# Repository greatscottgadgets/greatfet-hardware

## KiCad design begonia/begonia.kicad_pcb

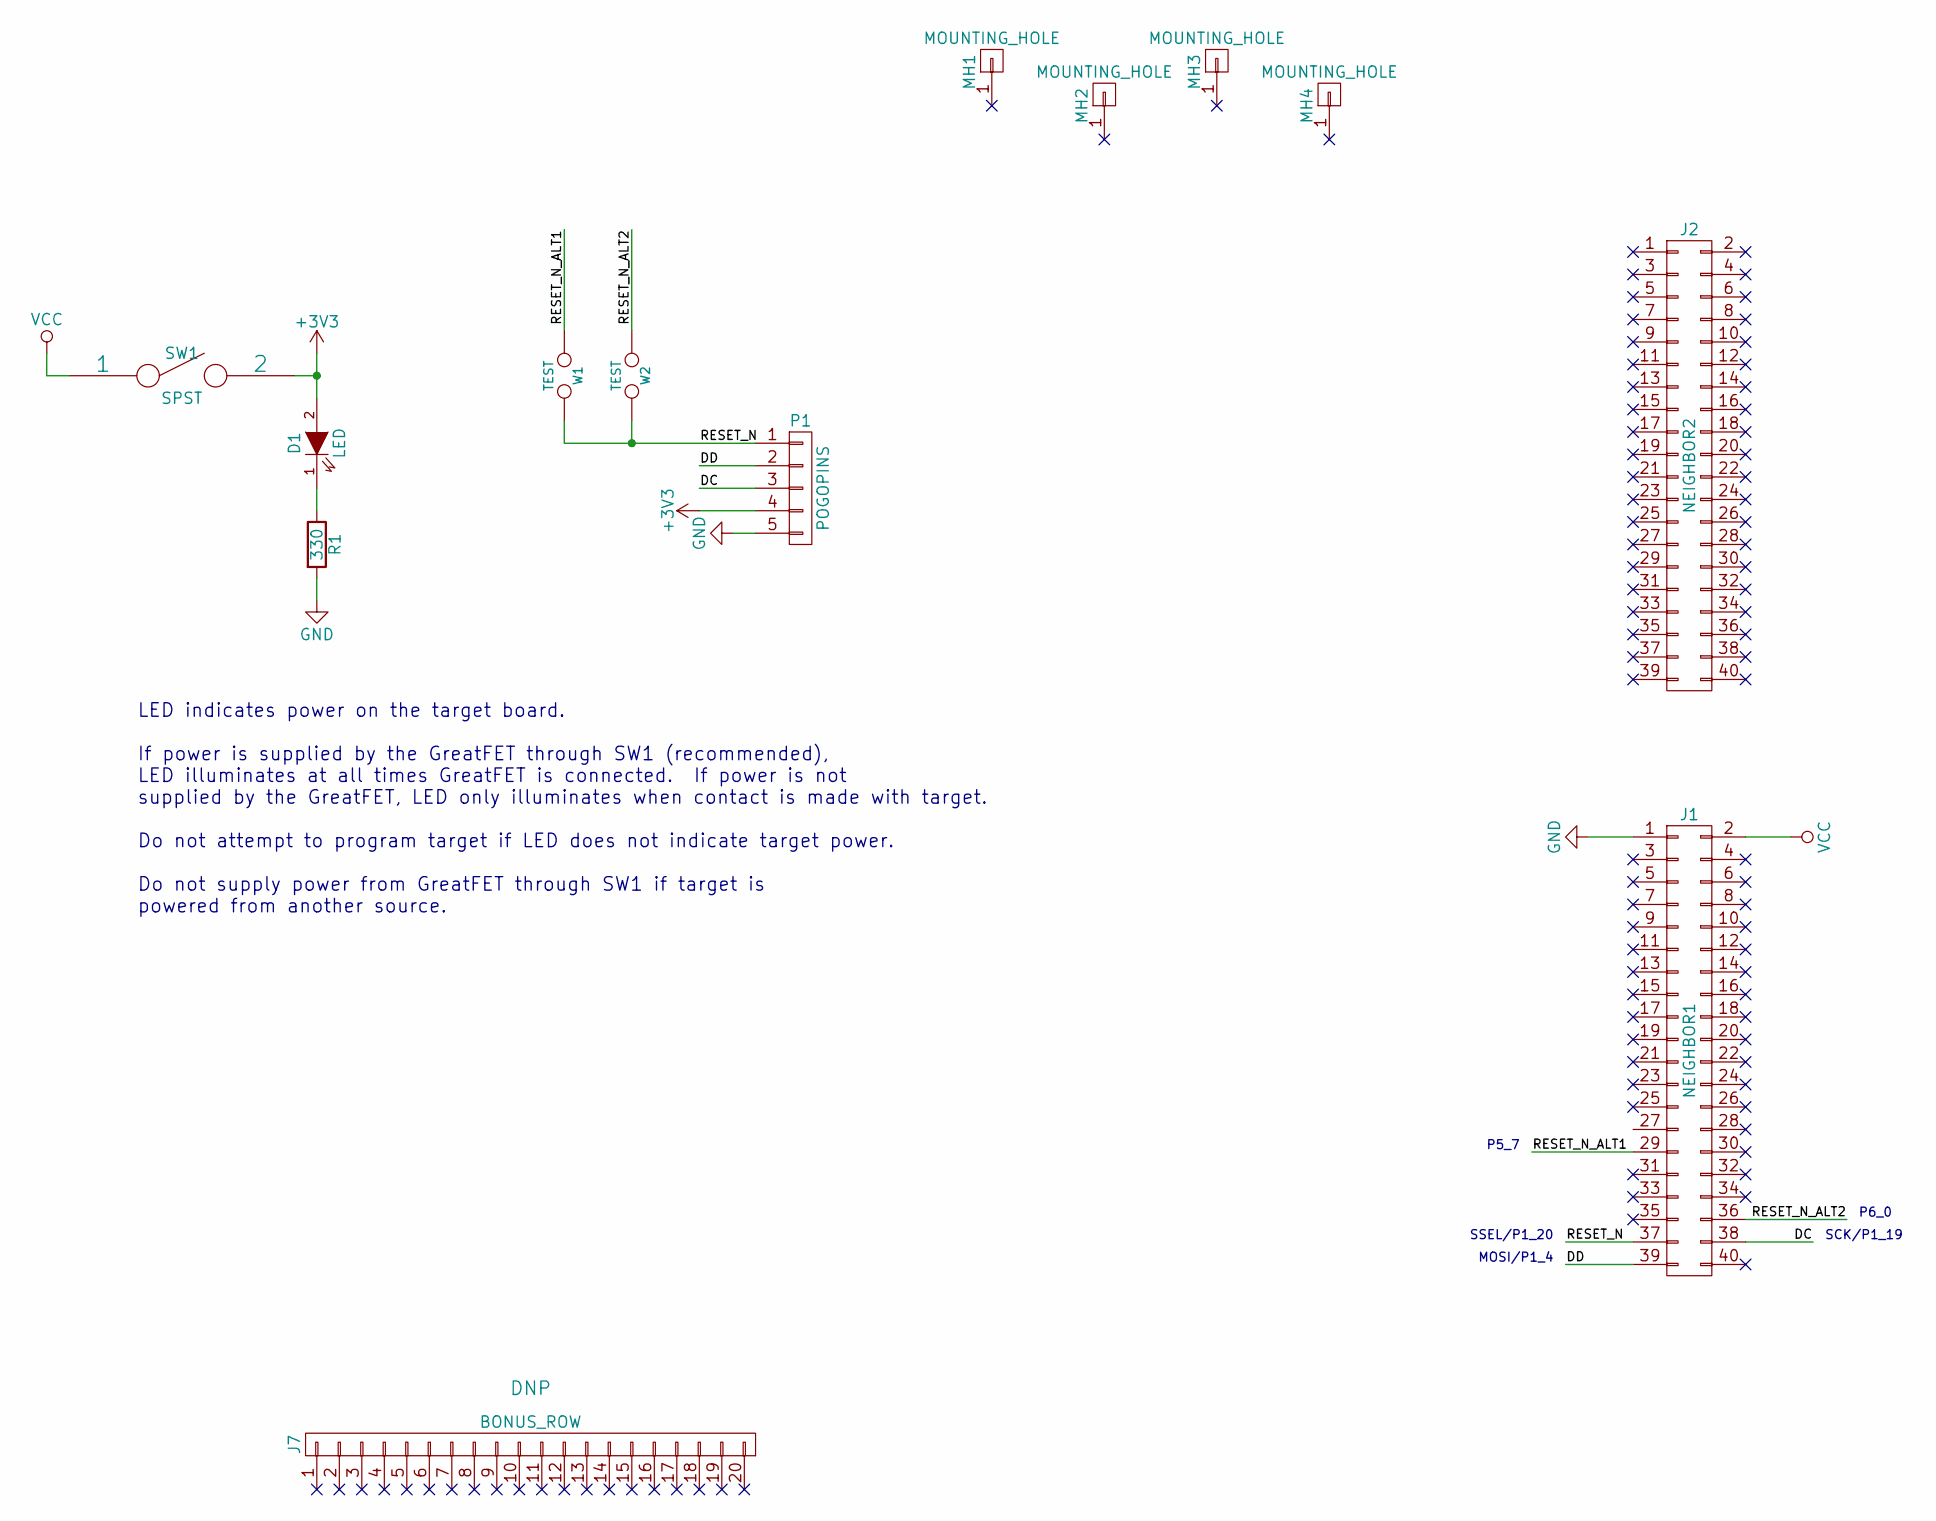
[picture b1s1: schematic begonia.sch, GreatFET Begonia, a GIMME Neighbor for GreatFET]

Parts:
D1: LED; 0603D; Part Number APT1608SGC
J1: NEIGHBOR1; HEADER-2x20; Part Number SSQ-120-23-G-D
J2: NEIGHBOR2; HEADER-2x20; Part Number SSQ-120-23-G-D
J7: BONUS_ROW; HEADER-1x20; Part Number SSQ-120-23-G-S
MH1, MH2, MH3, MH4: MOUNTING_HOLE; HOLE126MIL-COPPER
P1: POGOPINS; POGOPIN-5-IMME; Part Number PRT-09174
R1: 330; 0603; Part Number RMCF0603JT330R
SW1: SPST; SSSS810701; Part Number SSSS810701
W1, W2: TEST; 0603-JUMPER

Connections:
+3V3: D1.2 (A), P1.4, SW1.2
/DC: J1.38, P1.3
/DD: J1.39, P1.2
/RESET_N: J1.37, P1.1, W1.2, W2.2
/RESET_N_ALT1: J1.29, W1.1
/RESET_N_ALT2: J1.36, W2.1
GND: J1.1, P1.5, R1.2
unnamed: D1.1 (K), R1.1
VCC: J1.2, SW1.1

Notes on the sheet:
MOSI/P1_4
SCK/P1_19
SSEL/P1_20
LED indicates power on the target board. If power is supplied by the GreatFET through SW1 (recommended), LED illuminates at all times GreatFET is connected. If power is not supplied by the GreatFET, LED only illuminates when contact is made with target. Do not attempt to program target if LED does 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
P5_7
P6_0

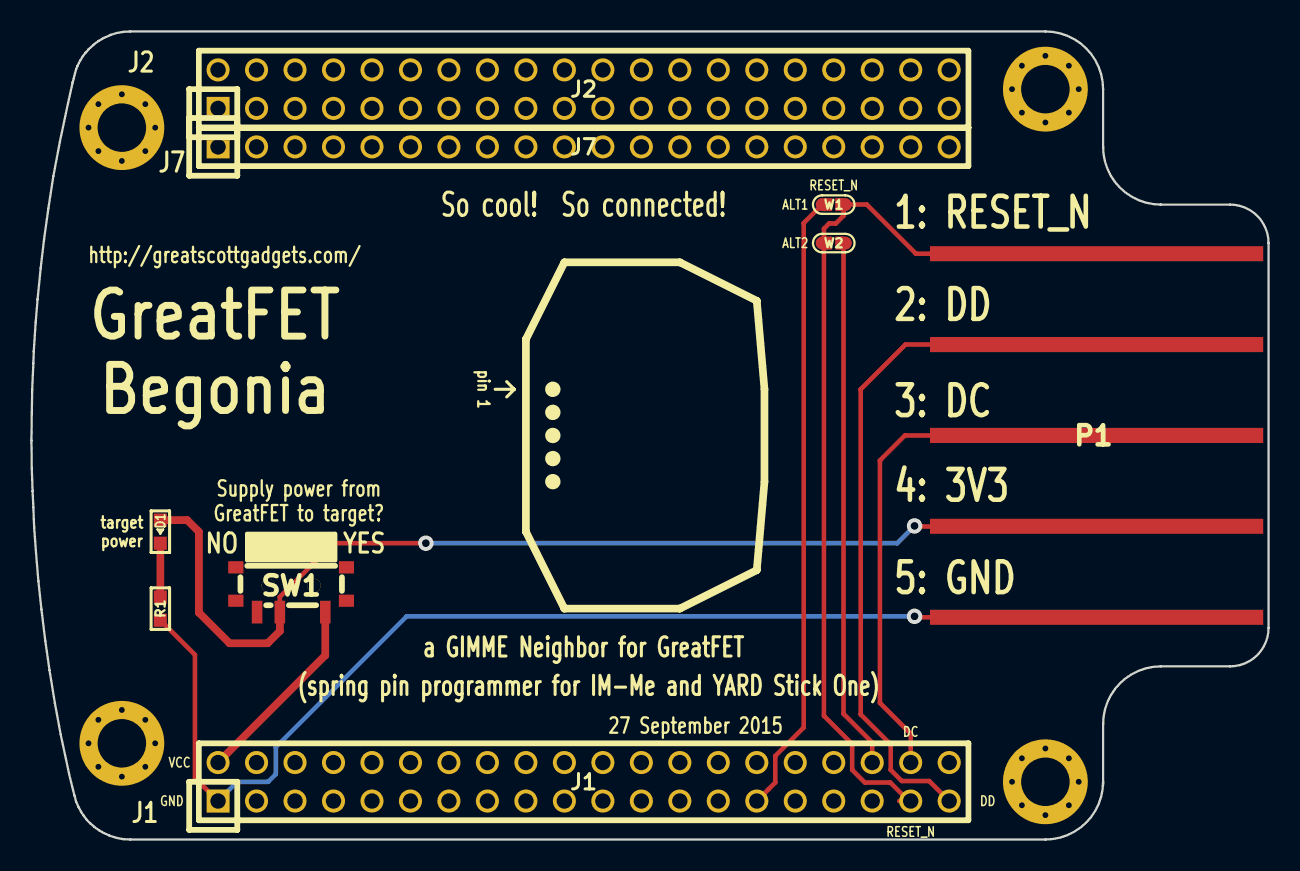
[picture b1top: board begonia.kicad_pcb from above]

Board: 2 copper layers, 81.7 x 53.3 mm, 13 parts (0 on the bottom side), 9 nets.

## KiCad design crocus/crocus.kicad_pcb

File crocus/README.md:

# GreatFET Crocus
A GreatFET Neighbor for the Nordic nRF24L01+

Required KiCad dependency:

https://github.com/greatscottgadgets/gsg-kicad-lib

If you are using git, the preferred way to install gsg-kicad-lib is to use the
submodule:

$ git submodule init && git submodule update

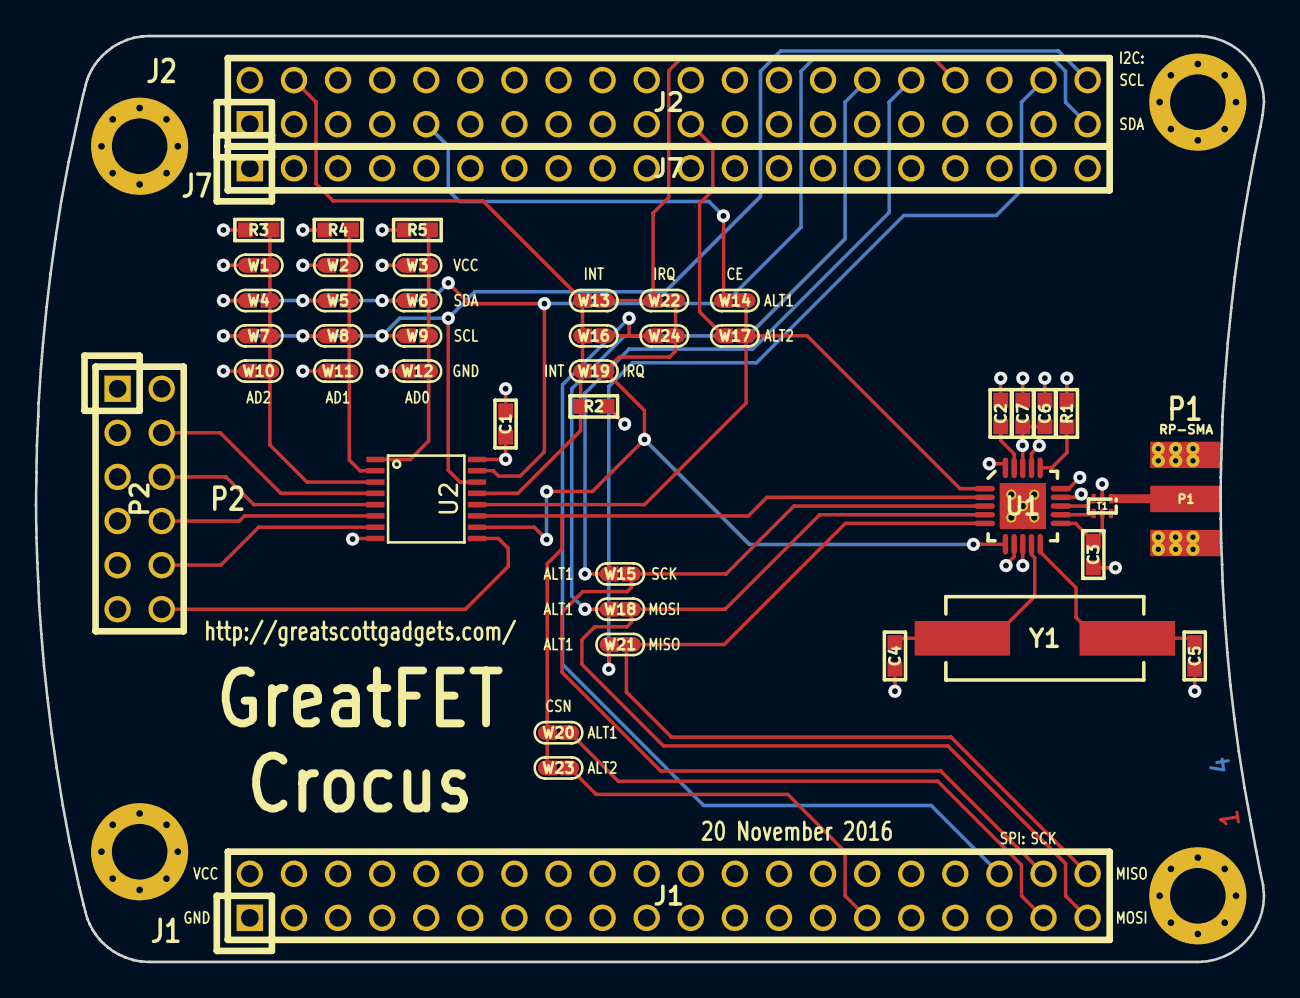
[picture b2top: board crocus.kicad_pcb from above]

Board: 4 copper layers, 70.7 x 53.3 mm, 49 parts (0 on the bottom side), 36 nets.

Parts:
C1, C2: 33nF; 0603
C3: 2.2nF; 0603
C4, C5: 18pF; 0603
C6: 10nF; 0603
C7: 1nF; 0603
J1: NEIGHBOR1; HEADER-2x20
J2: NEIGHBOR2; HEADER-2x20
J7: BONUS_ROW; HEADER-1x20
MH1, MH2, MH3, MH4: MOUNTING_HOLE; HOLE126MIL-COPPER
P1: RP-SMA; SMA-EDGE
P2: EXPANSION; HEADER-2x6
R1: 22.0k; 0603
R2, R3, R4, R5: 10k; 0603
T1: BALUN; 2500BL14M100
U1: nRF24L01+; QFN20-4
U2: PCA9674; TSSOP16
W1, W2, W3, W4, W5, W6, W7, W8, W9, W10, W11, W12, W13, W14, W15, W16, W17, W18, W19, W20, W21, W22, W23, W24: TEST; 0603-JUMPER
Y1: XTAL; HC-49S

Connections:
/AD0: R5.1, U2.1, W3.2, W6.2, W9.2, W12.2
/AD1: R4.1, U2.2, W2.2, W5.2, W8.2, W11.2
/AD2: R3.1, U2.3, W1.2, W4.2, W7.2, W10.2
/ANT1: T1.4, U1.12
/ANT2: T1.3, U1.13
/CE: U1.1, U2.12, W14.2, W17.2
/CE_ALT1: J2.9, W14.1
/CE_ALT2: J2.21, W17.1
/CSN: U1.2, U2.11, W20.2, W23.2
/CSN_ALT1: J1.37, W20.1
/CSN_ALT2: J1.29, W23.1
/DVDD: C2.1, U1.19
/I2C0_SCL: J2.40, U2.14, W7.1, W8.1, W9.1
/I2C0_SDA: J2.39, U2.15, W4.1, W5.1, W6.1
/INT: J2.4, R2.2, U2.13, W13.2, W16.2, W19.1
/INT_ALT1: J2.34, W13.1, W22.1
/INT_ALT2: J1.36, W16.1, W24.1
/IREF: R1.2, U1.16
/IRQ: U1.6, U2.10, W19.2, W22.2, W24.2
/MISO: J1.40, U1.5, W21.2
/MISO_ALT1: J2.38, W21.1
/MOSI: J1.39, U1.4, W18.2
/MOSI_ALT1: J2.30, W18.1
/P0: P2.4, U2.4
/P1: P2.6, U2.5
/P2: P2.8, U2.6
/P3: P2.10, U2.7
/P4: P2.12, U2.9
/RF: P1.1, T1.1
/SCK: J1.38, U1.3, W15.2
/SCK_ALT1: J2.32, W15.1
/VDD_PA: C3.1, T1.5, U1.11
/XC1: C5.1, U1.10, Y1.2
/XC2: C4.1, U1.9, Y1.1
GND: C1.2, C2.2, C3.2, C4.2, C5.2, C6.2, C7.2, J1.1, MH1.1, MH2.1, MH3.1, MH4.1, P1.2, P2.1, P2.3, P2.5, P2.7, P2.9, P2.11, R1.1, R3.2, R4.2, R5.2, T1.2, U1.8, U1.14, U1.17, U1.20, U2.8, W10.1, W11.1, W12.1
VCC: C1.1, C6.1, C7.1, J1.2, P2.2, R2.1, U1.7, U1.15, U1.18, U2.16, W1.1, W2.1, W3.1

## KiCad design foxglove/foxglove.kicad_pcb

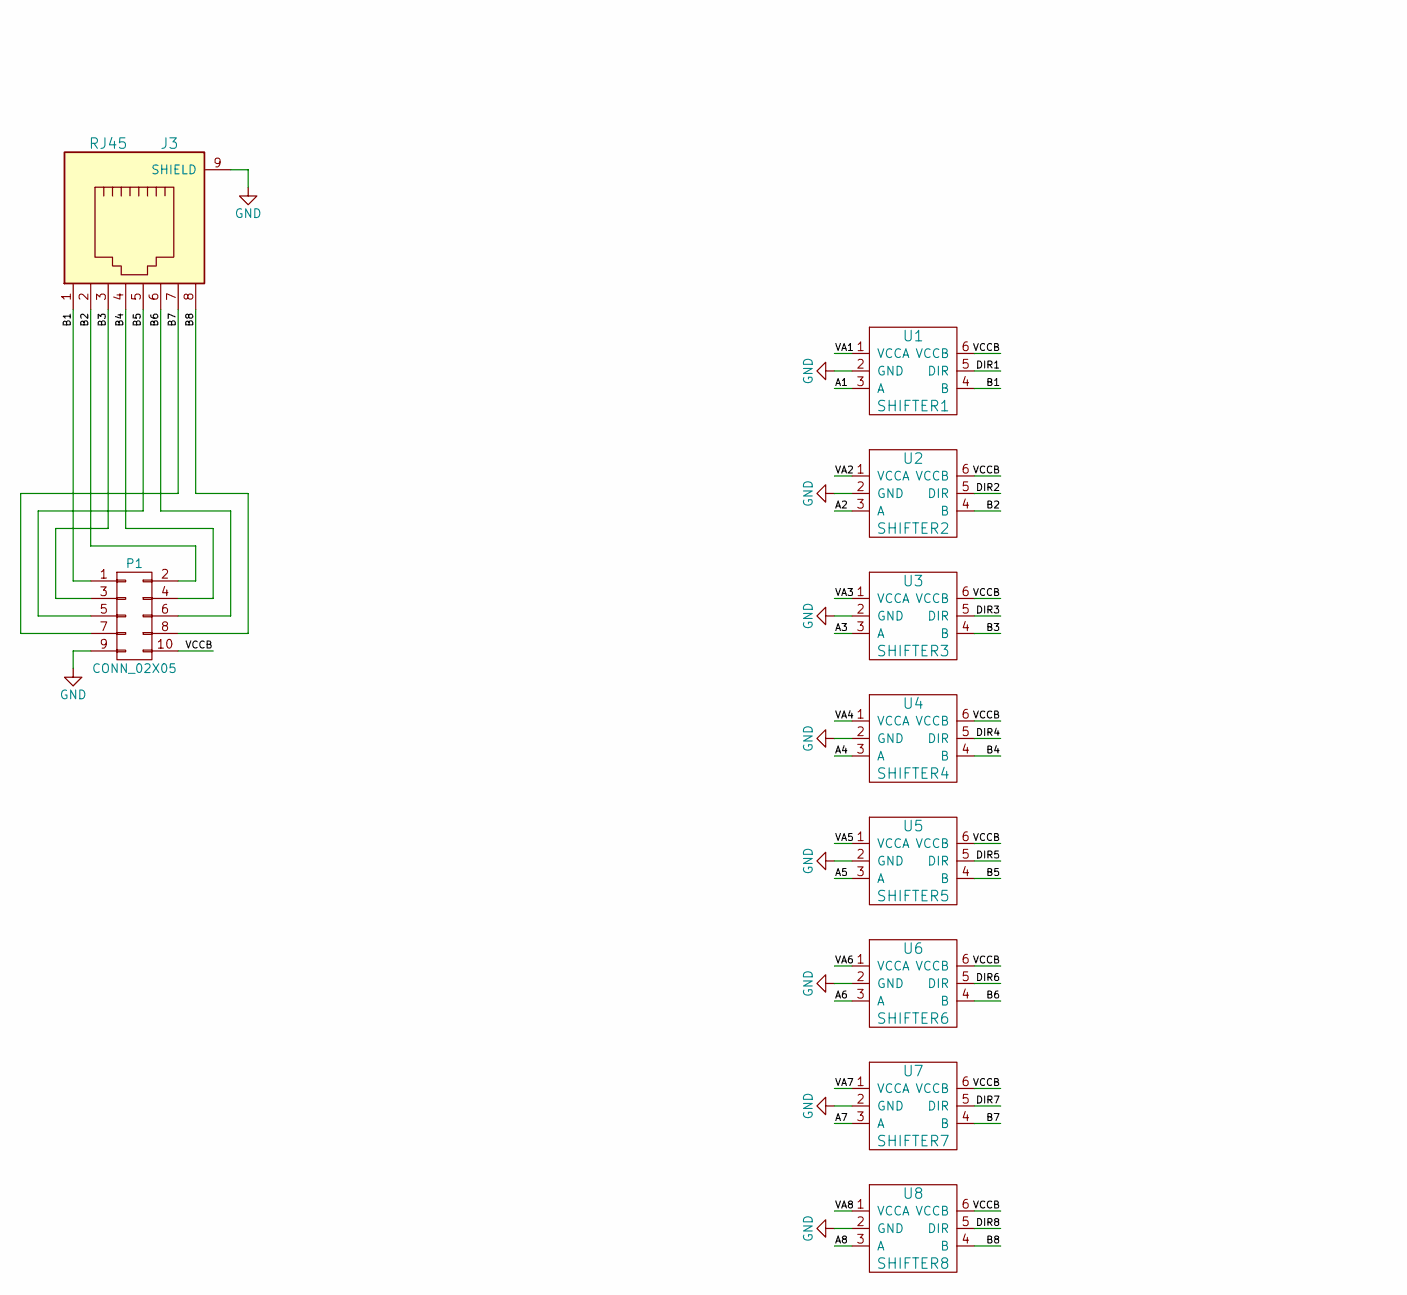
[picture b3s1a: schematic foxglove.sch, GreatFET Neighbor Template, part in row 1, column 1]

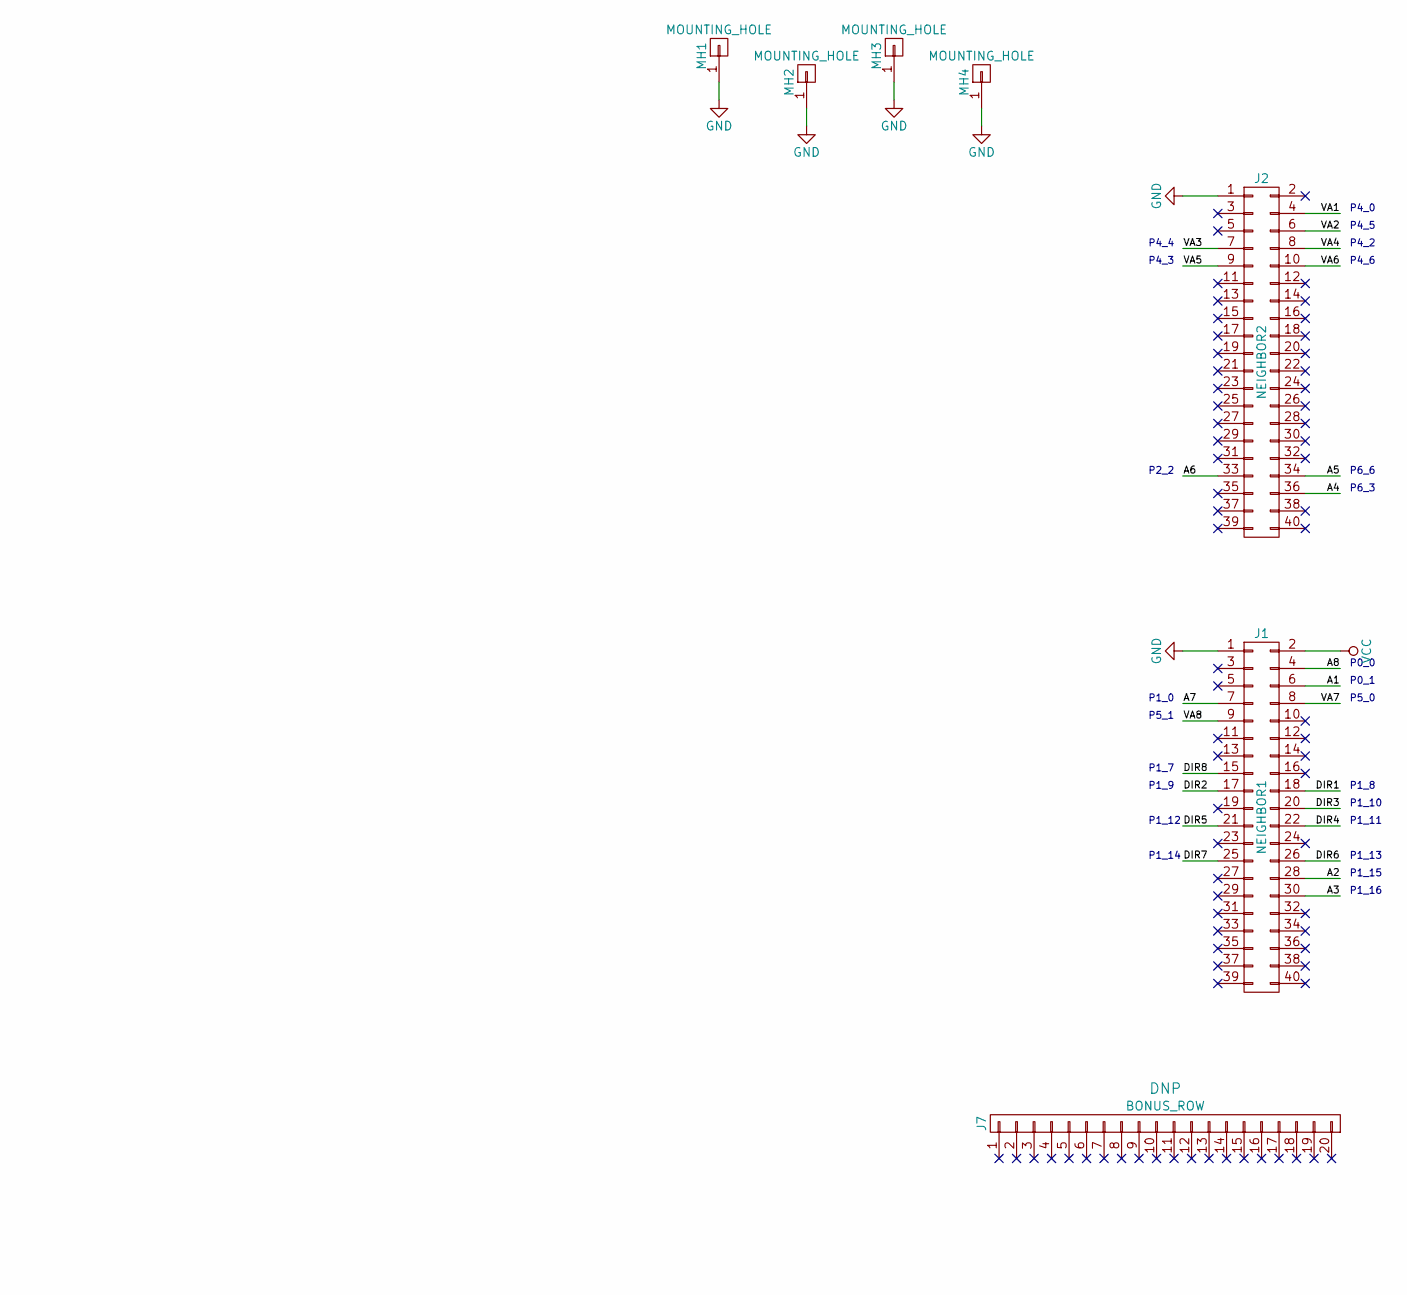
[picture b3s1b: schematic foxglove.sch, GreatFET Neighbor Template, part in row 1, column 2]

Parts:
J1: NEIGHBOR1; HEADER-2x20; Part Number SSQ-120-23-G-D
J2: NEIGHBOR2; HEADER-2x20; Part Number SSQ-120-23-G-D
J3: RJ45; RJ45-RJHSE-5380
J7: BONUS_ROW; HEADER-1x20; Part Number SSQ-120-23-G-S
MH1, MH2, MH3, MH4: MOUNTING_HOLE; HOLE126MIL-COPPER
P1: CONN_02X05; HEADER-2x5
U1: SHIFTER1; SOT363; Part Number 74LVCH1T45GW,125
U2: SHIFTER2; SOT363; Part Number 74LVCH1T45GW,125
U3: SHIFTER3; SOT363; Part Number 74LVCH1T45GW,125
U4: SHIFTER4; SOT363; Part Number 74LVCH1T45GW,125
U5: SHIFTER5; SOT363; Part Number 74LVCH1T45GW,125
U6: SHIFTER6; SOT363; Part Number 74LVCH1T45GW,125
U7: SHIFTER7; SOT363; Part Number 74LVCH1T45GW,125
U8: SHIFTER8; SOT363; Part Number 74LVCH1T45GW,125

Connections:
/A1: J1.6, U1.3 (A)
/A2: J1.28, U2.3 (A)
/A3: J1.30, U3.3 (A)
/A4: J2.36, U4.3 (A)
/A5: J2.34, U5.3 (A)
/A6: J2.33, U6.3 (A)
/A7: J1.7, U7.3 (A)
/A8: J1.4, U8.3 (A)
/B1: J3.1, P1.1, U1.4 (B)
/B2: J3.2, P1.2, U2.4 (B)
/B3: J3.3, P1.3, U3.4 (B)
/B4: J3.4, P1.4, U4.4 (B)
/B5: J3.5, P1.5, U5.4 (B)
/B6: J3.6, P1.6, U6.4 (B)
/B7: J3.7, P1.7, U7.4 (B)
/B8: J3.8, P1.8, U8.4 (B)
/DIR1: J1.18, U1.5 (DIR)
/DIR2: J1.17, U2.5 (DIR)
/DIR3: J1.20, U3.5 (DIR)
/DIR4: J1.22, U4.5 (DIR)
/DIR5: J1.21, U5.5 (DIR)
/DIR6: J1.26, U6.5 (DIR)
/DIR7: J1.25, U7.5 (DIR)
/DIR8: J1.15, U8.5 (DIR)
/VA1: J2.4, U1.1 (VCCA)
/VA2: J2.6, U2.1 (VCCA)
/VA3: J2.7, U3.1 (VCCA)
/VA4: J2.8, U4.1 (VCCA)
/VA5: J2.9, U5.1 (VCCA)
/VA6: J2.10, U6.1 (VCCA)
/VA7: J1.8, U7.1 (VCCA)
/VA8: J1.9, U8.1 (VCCA)
/VCCB: P1.10, U1.6 (VCCB), U2.6 (VCCB), U3.6 (VCCB), U4.6 (VCCB), U5.6 (VCCB), U6.6 (VCCB), U7.6 (VCCB), U8.6 (VCCB)
GND: J1.1, J2.1, J3.9 (SHIELD), MH1.1, MH2.1, MH3.1, MH4.1, P1.9, U1.2 (GND), U2.2 (GND), U3.2 (GND), U4.2 (GND), U5.2 (GND), U6.2 (GND), U7.2 (GND), U8.2 (GND); also elsewhere on the board
VCC: J1.2; also elsewhere on the board

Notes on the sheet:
P0_0
P0_1
P1_15
P1_16
P6_3
P6_6
P1_0
P1_7
P1_8
P1_9
P1_10
P1_11
P1_12
P1_13
P1_14
P2_2
P4_0
P4_5
P4_2
P4_6
P4_4
P4_3
P5_0
P5_1

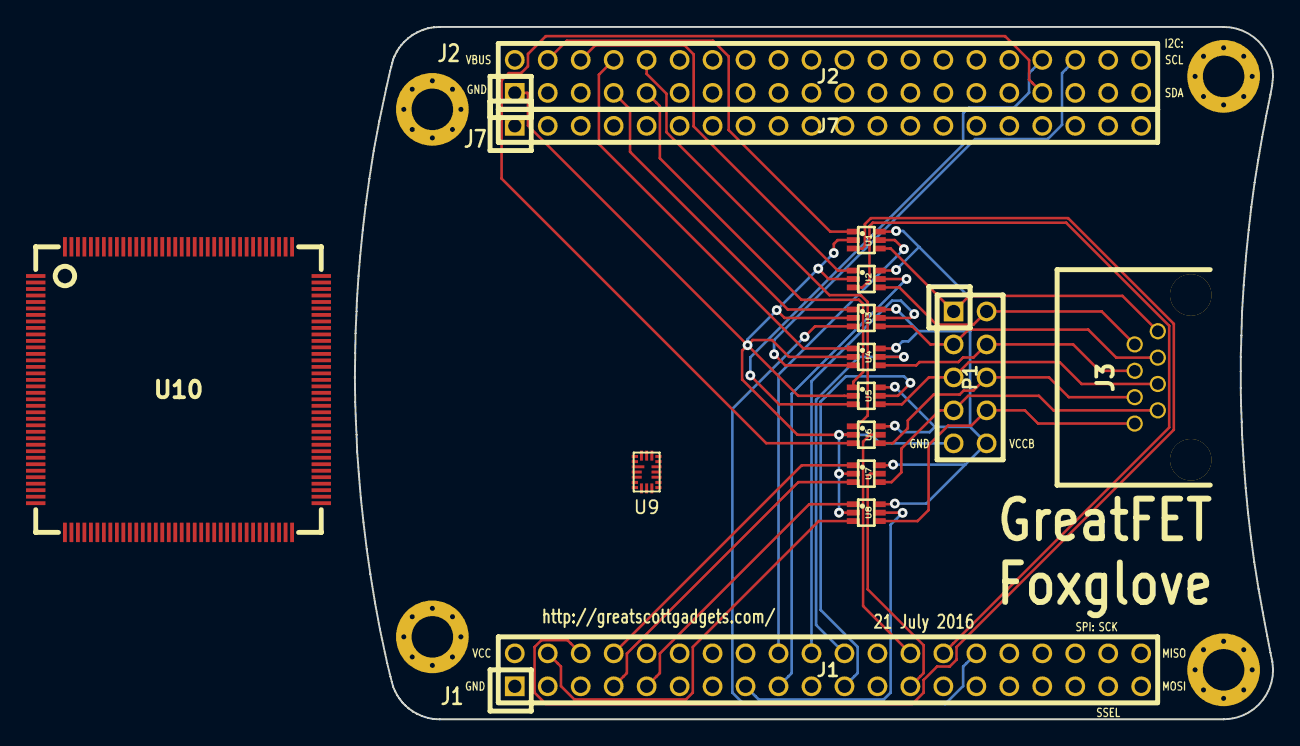
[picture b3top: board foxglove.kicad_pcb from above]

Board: 2 copper layers, 70.7 x 53.3 mm, 19 parts (0 on the bottom side), 35 nets.

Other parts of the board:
U9: SLG46621
U10: iCE40HX4K; LQFP144

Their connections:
GND: U9.11; also elsewhere on the board
VCC: U9.1; also elsewhere on the board

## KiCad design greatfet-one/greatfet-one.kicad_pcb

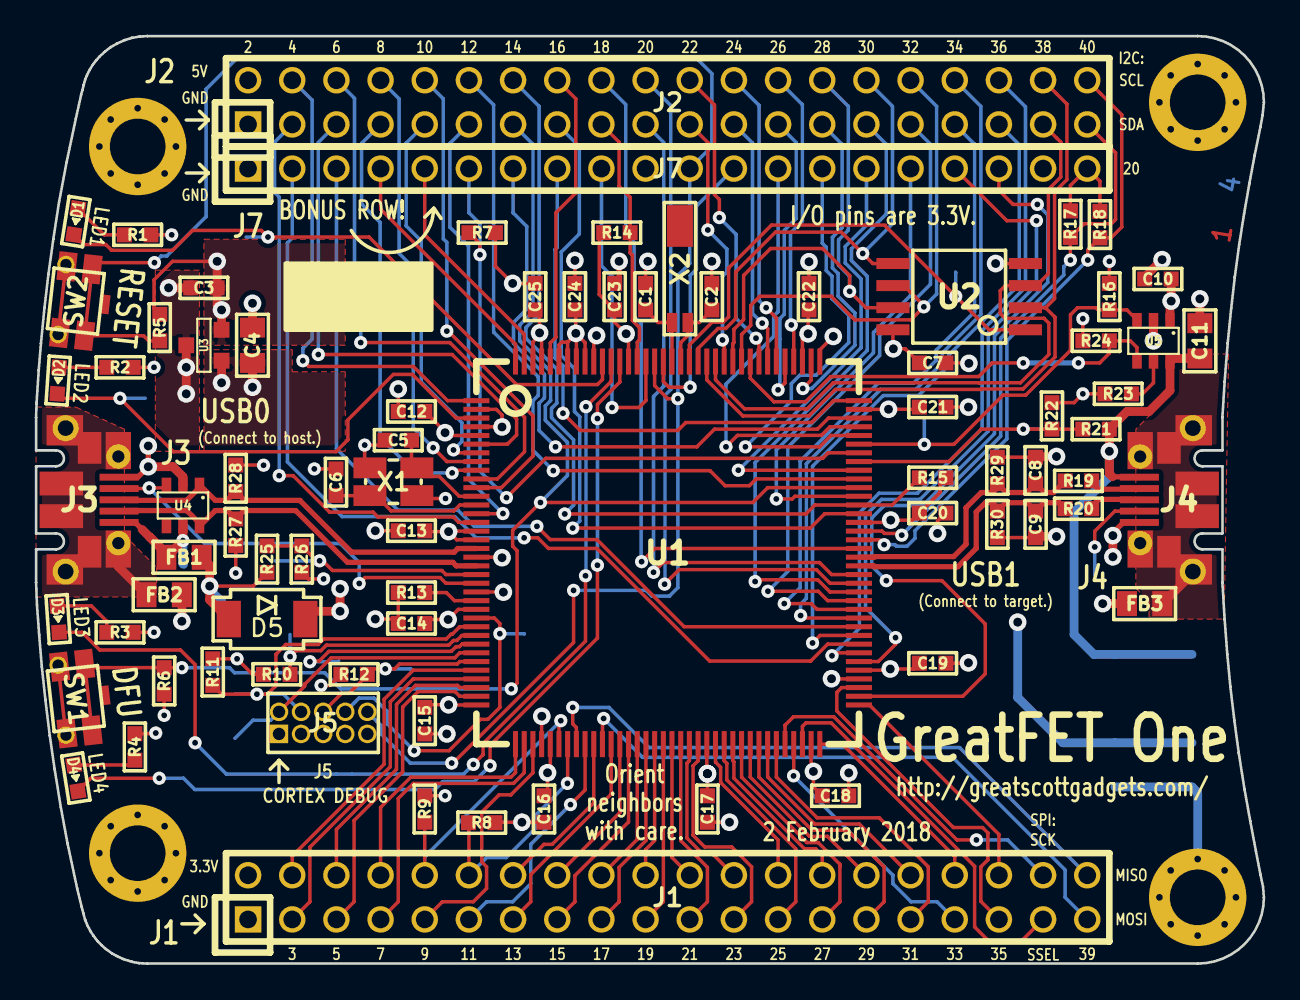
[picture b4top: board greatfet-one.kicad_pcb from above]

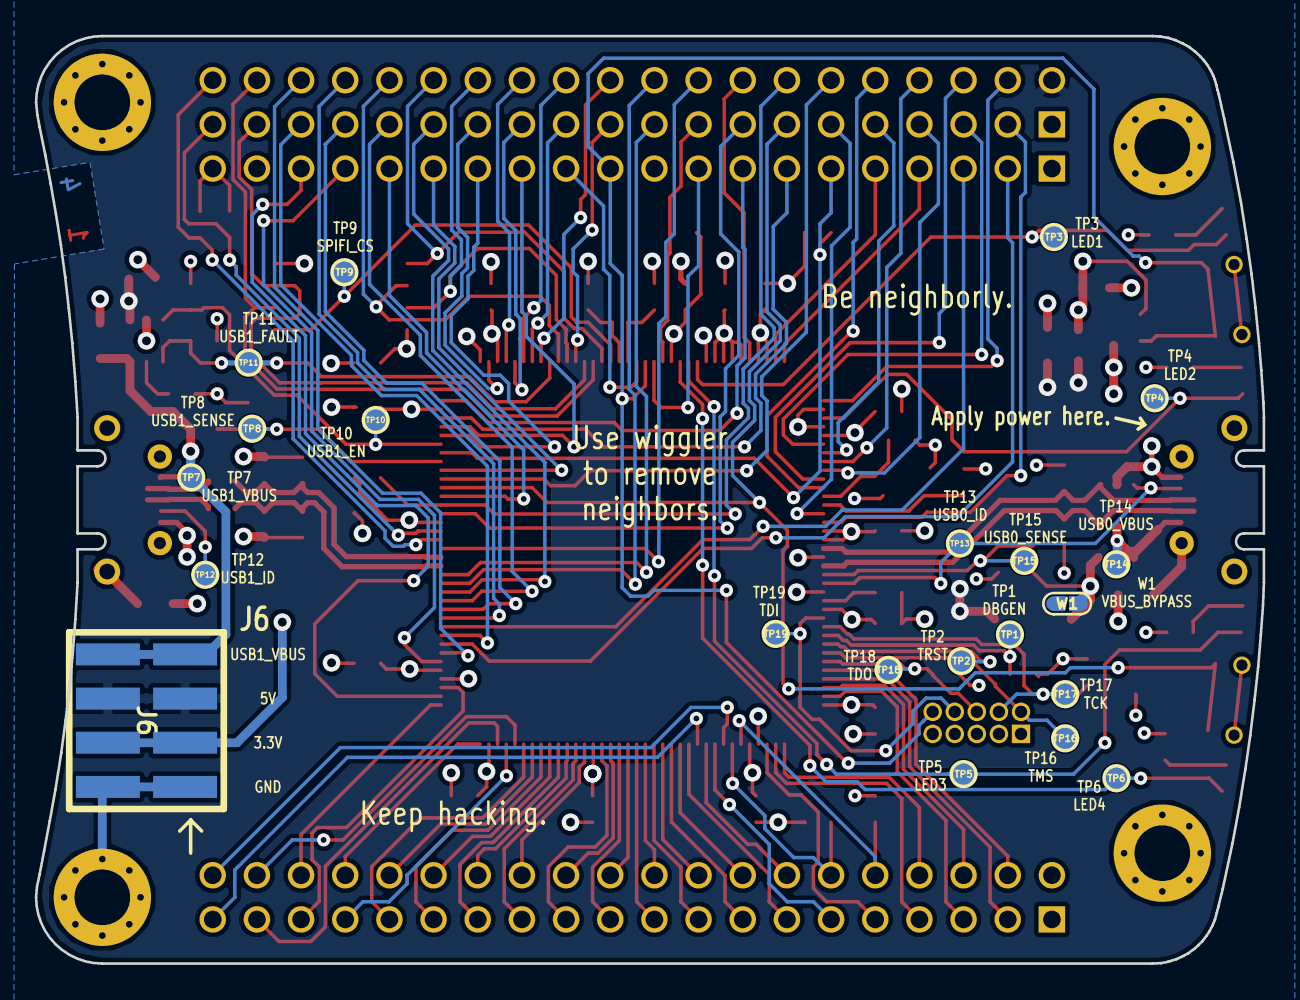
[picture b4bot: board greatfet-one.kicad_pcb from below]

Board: 4 copper layers, 70.6 x 53.3 mm, 103 parts (21 on the bottom side), 133 nets.

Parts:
C1, C2, C5, C6, C8, C9: 18pF; 0603
C3, C10: 1uF; 0603
C4, C11: 10uF; 0805
C7, C12, C13, C14, C15, C16, C17, C18, C19, C20, C21, C22, C23, C24, C25: 100nF; 0603
D1: LED1; 0603D
D2: LED2; 0603D
D3: LED3; 0603D
D4: LED4; 0603D
D5: VBUS_DIODE; SOD128
FB1, FB2, FB3: FILTER; 0805
J1: NEIGHBOR1; HEADER-2x20
J2: NEIGHBOR2; HEADER-2x20
J3, J4: USB-MICRO-B-SHIELDED; USB-MICROB-FCI-10103592-LONGPADS
J5: JTAG; 50MIL-HEADER-2x5-TH
J6: POWER; HEADER-SMT-2x4
J7: BONUS_ROW; HEADER-1x20
MH1, MH2, MH3, MH4: MOUNTING_HOLE; HOLE126MIL-COPPER
R1, R2, R3, R4: 330; 0603
R5, R6, R7, R8, R9, R10, R11, R12, R14, R15, R16, R21, R24, R25: 10k; 0603
R13: 12.0k; 0603
R17, R18: 1.8k; 0603
R19, R20: 33.0; 0603
R22, R26: 18k; 0603
R23: 43.2k; 0603
R27, R28, R29, R30: 15k; 0603
SW1: DFU; SWITCH-PTS840-P
SW2: RESET; SWITCH-PTS840-P
TP1: DBGEN; TESTPOINT-50MIL
TP2: TRST; TESTPOINT-50MIL
TP3: LED1; TESTPOINT-50MIL
TP4: LED2; TESTPOINT-50MIL
TP5: LED3; TESTPOINT-50MIL
TP6: LED4; TESTPOINT-50MIL
TP7: USB1_VBUS; TESTPOINT-50MIL
TP8: USB1_SENSE; TESTPOINT-50MIL
TP9: SPIFI_CS; TESTPOINT-50MIL
TP10: USB1_EN; TESTPOINT-50MIL
TP11: USB1_FAULT; TESTPOINT-50MIL
TP12: USB1_ID; TESTPOINT-50MIL
TP13: USB0_ID; TESTPOINT-50MIL
TP14: USB0_VBUS; TESTPOINT-50MIL
TP15: USB0_SENSE; TESTPOINT-50MIL
TP16: TMS; TESTPOINT-50MIL
TP17: TCK; TESTPOINT-50MIL
TP18: TDO; TESTPOINT-50MIL
TP19: TDI; TESTPOINT-50MIL
U1: LPC4330FBD144; LQFP144
U2: W25Q16DV; SOIC8-208
U3: AP7333; SOT23-3
U4: IP4220CZ6; SOT457
U5: AP2553W6-7; SOT457
W1: VBUS_BYPASS; 0603-JUMPER
X1: MCU_XTAL; XTAL3.2x2.5mm-EXT
X2: RTC_XTAL; XTAL-AB26TRQ

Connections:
+5V: C4.1, C10.1, D5.1, J2.2, J6.5, J6.6, U3.1, U5.1, W1.1
/ADC0_0: J2.5, U1.6
/ADC0_2: J7.5, U1.143
/ADC0_5: J7.4, U1.144
/CLK0: J1.11, U1.45
/CLK2: J2.12, U1.99
/DBGEN: R10.2, TP1.1, U1.28
/I2C0_SCL: J2.40, R18.2, U1.92
/I2C0_SDA: J2.39, R17.2, U1.93
/LED1: D1.1, TP3.1, U1.134
/LED2: D2.1, TP4.1, U1.3
/LED3: D3.1, TP5.1, U1.133
/LED4: D4.1, TP6.1, U1.132
/P0_0: J1.4, U1.32
/P0_1: J1.6, U1.34
/P1_0: J1.7, U1.38
/P1_1: J1.10, R9.2, U1.42
/P1_2: J1.12, R8.1, U1.43
/P1_3: J1.40, U1.44
/P1_4: J1.39, U1.47
/P1_5: J1.13, U1.48
/P1_6: J1.16, U1.49
/P1_7: J1.15, U1.50
/P1_8: J1.18, U1.51
/P1_9: J1.17, U1.52
/P1_10: J1.20, U1.53
/P1_11: J1.22, U1.55
/P1_12: J1.21, U1.56
/P1_13: J1.26, U1.60
/P1_14: J1.25, U1.61
/P1_15: J1.28, U1.62
/P1_16: J1.30, U1.64
/P1_17: J1.32, U1.66
/P1_18: J1.31, U1.67
/P1_19: J1.38, U1.68
/P1_20: J1.37, U1.70
/P2_0: J1.35, U1.75
/P2_1: J2.35, U1.81
/P2_2: J2.33, U1.84
/P2_3: J2.20, U1.87
/P2_4: J2.19, U1.88
/P2_5: J2.18, U1.91
/P2_6: J2.15, U1.95
/P2_7: J2.14, R15.2, U1.96
/P2_8: J2.13, R6.1, SW1.1, U1.98
/P2_9: J7.6, R7.1, U1.102
/P2_10: J7.14, U1.104
/P2_11: J7.13, U1.105
/P2_12: J7.7, U1.106
/P2_13: J7.8, U1.108
/P3_0: J2.26, U1.112
/P3_1: J2.24, U1.114
/P3_2: J2.22, U1.116
/P3_3: J2.32, U1.118, U2.6
/P3_4: J2.28, U1.119, U2.7
/P3_5: J2.37, U1.121, U2.3
/P3_6: J2.38, U1.122, U2.2
/P3_7: J2.30, U1.123, U2.5
/P4_0: J2.4, U1.1
/P4_2: J2.8, U1.8
/P4_3: J2.9, U1.7
/P4_4: J2.7, U1.9
/P4_5: J2.6, U1.10
/P4_6: J2.10, U1.11
/P4_7: J2.11, U1.14
/P4_8: J2.3, U1.15
/P4_9: J1.3, U1.33
/P4_10: J1.5, U1.35
/P5_0: J1.8, U1.37
/P5_1: J1.9, U1.39
/P5_2: J1.14, U1.46
/P5_3: J1.19, U1.54
/P5_4: J1.24, U1.57
/P5_5: J1.23, U1.58
/P5_6: J1.27, U1.63
/P5_7: J1.29, U1.65
/P6_0: J1.36, U1.73
/P6_1: J7.18, U1.74
/P6_2: J7.17, U1.78
/P6_3: J2.36, U1.79
/P6_4: J7.2, U1.80
/P6_5: J7.3, U1.82
/P6_6: J2.34, U1.83
/P6_7: J2.31, U1.85
/P6_8: J2.29, U1.86
/P6_9: J7.16, U1.97
/P6_10: J7.15, U1.100
/P7_0: J2.27, U1.110
/P7_1: J2.25, U1.113
/P7_2: J2.23, U1.115
/P7_7: J2.16, U1.140
/P9_5: J1.33, U1.69
/P9_6: J1.34, U1.72
/PF_4: J2.21, U1.120
/RESET: J5.10, J7.11, R5.2, SW2.1, U1.128
/RTCX1: C2.1, U1.125, X2.2
/RTCX2: C1.1, U1.126, X2.1
/RTC_ALARM: J7.9, U1.129
/SPIFI_CS: TP9.1, U1.124, U2.1
/TCK: J5.4, R11.2, TP17.1, U1.27
/TDI: J5.8, TP19.1, U1.26
/TDO: J5.6, R12.2, TP18.1, U1.31
/TMS: J5.2, TP16.1, U1.30
/TRST: TP2.1, U1.29
/USB0_D+: J3.3, R28.1, U1.18, U4.1
/USB0_D-: J3.2, R27.1, U1.20, U4.6
/USB0_ID: J3.4, TP13.1, U1.22, U4.3
/USB0_SENSE: R25.2, R26.2, TP15.1, U1.21
/USB0_SHIELD: FB2.2, J3.0
/USB0_VBUS: FB1.1, J3.1, TP14.1, U4.5
/USB1_D+: C9.1, R20.2, R30.1, U1.89
/USB1_D-: C8.1, R19.2, R29.1, U1.90
/USB1_EN: R16.2, TP10.1, U1.103, U5.3
/USB1_FAULT: R24.1, TP11.1, U1.117, U5.4
/USB1_ID: J4.4, TP12.1
/USB1_SENSE: R21.2, R22.2, TP8.1, U1.101
/USB1_SHIELD: FB3.1, J4.0
/USB1_VBUS: C11.1, J4.1, J6.7, J6.8, R21.1, TP7.1, U5.6
/VBAT: J7.12, U1.127
/WAKEUP0: J2.17, R14.2, U1.130
GND: C1.2, C2.2, C3.2, C4.2, C5.2, C6.2, C7.2, C8.2, C9.2, C10.2, C11.2, C12.2, C13.2, C14.2, C15.2, C16.2, C17.2, C18.2, C19.2, C20.2, C21.2, C22.2, C23.2, C24.2, C25.2, FB2.1, FB3.2, J1.1, J2.1, J3.5, J4.5, J5.3, J5.5, J5.9, J6.1, J6.2, J7.1, J7.10, J7.19, MH1.1, MH2.1, MH3.1, MH4.1, R6.2, R7.2, R8.2, R13.2, R16.1, R22.1, R23.1, R26.1, R27.2, R28.2, R29.2, R30.2, SW2.2, U1.2, U1.4, U1.19, U1.23, U1.40, U1.76, U1.109, U1.135, U2.4, U3.3, U4.2, U5.2, X1.2, X1.4
unnamed: C5.1, U1.12, X1.1
unnamed: C6.1, U1.13, X1.3
unnamed: D1.2, R1.2
unnamed: D2.2, R2.2
unnamed: D3.2, R3.2
unnamed: D4.2, R4.2
unnamed: D5.2, FB1.2, R25.1, W1.2
unnamed: J4.2, R19.1
unnamed: J4.3, R20.1
unnamed: R13.1, U1.24
unnamed: R23.2, U5.5
VCC: C3.1, C7.1, C12.1, C13.1, C14.1, C15.1, C16.1, C17.1, C18.1, C19.1, C20.1, C21.1, C22.1, C23.1, C24.1, C25.1, J1.2, J5.1, J6.3, J6.4, J7.20, R1.1, R2.1, R3.1, R4.1, R5.1, R9.1, R10.1, R11.1, R12.1, R14.1, R15.1, R17.1, R18.1, R24.2, SW1.2, U1.5, U1.16, U1.17, U1.25, U1.36, U1.41, U1.59, U1.71, U1.77, U1.94, U1.107, U1.111, U1.131, U1.136, U1.137, U1.138, U1.139, U1.141, U1.142, U2.8, U3.2

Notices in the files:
begonia/begonia.sch:
Copyright 2015 Michael Ossmann
License: GPL v2
